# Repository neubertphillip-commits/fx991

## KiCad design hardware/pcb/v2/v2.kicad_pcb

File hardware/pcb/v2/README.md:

# Hauptplatine V2 (Entwurf, nicht bestellfertig)

Tastaturplatine wie V1 plus alles, was sonst lose verdrahtet waere: Der XIAO ESP32S3 liegt mit
der Unterseite zur Platine auf deren Rueckseite und steckt per B2B in einer DF40-Buchse; Kamera,
Mikro und Kamera-Spannungsregler sitzen auf der Platine (Ersatz fuer die Sense-Platine, die mit
~15 mm zu hoch ist). Generator: `hauptplatine_v2.py` (nutzt `../tastatur_pcb.py`).
Vorschau: `vorschau_v2.png` (links vorn, rechts Rueckseite von hinten).

## Was drauf ist

| Ref | Teil | Funktion |
|---|---|---|
| K1-K50 | Kontaktkaemme (ENIG) | Tasten, Matrix 9x7 wie V1 |
| U1, C1, R1, R2 | MCP23017, 100 nF, 2x 4,7 kOhm | Tastatur-Scanner, I2C-Pull-ups |
| J10 | Hirose DF40C-30DS-0.4V (1,5 mm Stapelhoehe) | B2B zum XIAO: 3V3, GND, Kamera, Mikro, SPI, D2 |
| J11 | 8 Bruecken-Pads unter den XIAO-Kantenpads | D0 (INT), D1 (LCD-CS), D3 (Akku-Messung), D4/D5 (I2C), 5V, BAT-Pads |
| J12, U2, U3, FB1, R3, R4, C2-C7 | 24-pol. FPC (0,5 mm), 2x LDO | Kamera OV3660 |
| MIC1, C8 | MSM261D3526H1CPM | PDM-Mikro (GPIO 42 Takt, 41 Daten) |
| J13 | 8 Pads | LT7680-Displayboard: 3V3, GND, SCK, MOSI, MISO, CS (D1), RST (D2), WAIT (frei) |
| J14 | 2 Pads | LiPo (geht ueber J11 an die BAT-Pads des XIAO) |
| J15, D1 | 2 Pads, Schottky 10MQ060N | Qi-Empfaenger -> 5V-Pin des XIAO |
| R5, R6 | 2x 100 kOhm | Akkuspannung halbiert an D3 (statt LT7680-WAIT) |

Montage: XIAO mit Akku-Draehten zuerst auf die DF40-Buchse stecken; die Kantenpads und BAT-Pads
ueberbruecken den 1,5-mm-Spalt mit kurzen Drahtstuecken (Bauteilbeinchen) zu J11.

## Vor der Bestellung (offen, ohne das nicht bestellen)

1. **Lage der B2B-Buchse unter dem XIAO**: aus Seeeds Sense-Platine abgeleitet (Mitte 11,05 / 2,31 mm),
   aber angenommen, dass der Stecker am Ende gegenueber USB sitzt. Am echten XIAO nachmessen
   (Foto der Unterseite mit Lineal genuegt).
2. **DF40-Footprint und Pin-1-Lage**: Reihenabstand (hier 2,2 mm) und Padmasse aus der Hirose-Zeichnung,
   Pin 1 der Buchse gegen Seeeds Sense-Layout pruefen (Belegung siehe `../README.md`).
3. **Kamera-Spannungen**: AVDD 2,8 V ist sicher. DOVDD (FPC-Pin 11) hier 2,8 V, DVDD (Pin 10) ueber U3;
   Seeed nutzt laut Stueckliste ein 1,3-V-LDO, das Netz heisst aber VCC_1V8. Mit Seeeds Schaltplan-PDF
   klaeren (ESP32-S3 braucht >= 2,5 V High-Pegel, also DOVDD nicht 1,8 V). FPC-Pin 24 hat bei Seeed
   eine Diode (D6) - Funktion klaeren.
4. **FPC-Buchse und Pin 1**: Footprint AFC01-S24FCC-00 angenaehert; Pin-Reihenfolge zur Kamera pruefen.
5. **Mikro-Footprint** ist ein Platzhalter (Padlage aus dem Datenblatt uebernehmen; Schalloeffnung oben?).
6. **BAT-Polaritaet** der XIAO-Unterseitenpads (BAT1/BAT2) am XIAO ablesen und J14 beschriften.
7. **Hoehe**: XIAO ueber der Platine ~5 mm (1,5 mm Buchse + ~3,5 mm XIAO); hinter der Platine sind
   ~4 mm gemessen. Rueckdeckel-Wanne messen; sonst Rueckdeckel innen ausfraesen.
8. **Teile bei JLCPCB/LCSC**: DF40C-30DS-0.4V, AFC01-S24FCC-00, MSM261D3526H1CPM, ME6211-LDOs
   auf Verfuegbarkeit pruefen; sonst Ersatzteile mit gleichem Footprint.
9. Firmware: Matrix-Scan fuer V1/V2 (statt der 16 Casio-Leitungen), D3 als Akku-Messung.

## Neu erzeugen

```
python3 hauptplatine_v2.py
java -jar freerouting-2.4.1-executable.jar -de v2.dsn -do v2.ses -mp 60   # Java 25
python3 hauptplatine_v2.py --ses v2.ses
```

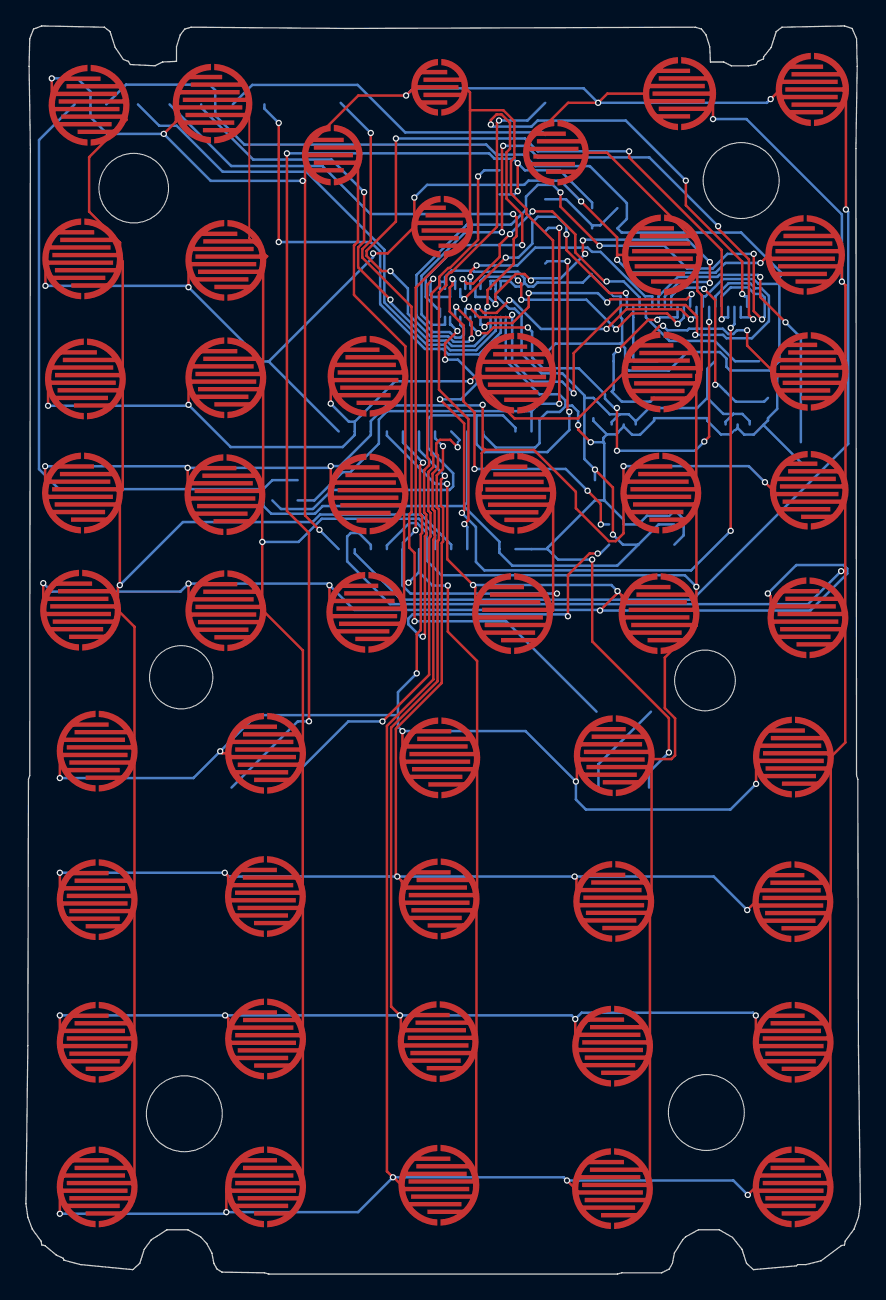
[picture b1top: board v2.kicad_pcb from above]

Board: 2 copper layers, 65.9 x 98.6 mm, 83 parts (0 on the bottom side), 52 nets.

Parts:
C1, C7, C8: 100nF
C2, C3, C4, C5, C6: 1uF
C9: 10uF
D1: 10MQ060NTRPBF
FB1: Ferrit 600R
H1, H2, H3, H4, H5, H6: (no value)
J10: DF40C-30DS-0.4V
J11: XIAO-Bruecken
J12: AFC01-S24FCC-00
J13: LT7680
J14: Akku
J15: Qi
K1, K2, K3, K4, K5, K6, K7, K8, K9, K10, K11, K12, K13, K14, K15, K16, K17, K18, K19, K20, K21, K22, K23, K24, K25, K26, K27, K28, K29, K30, K31, K32, K33, K34, K35, K36, K37, K38, K39, K40, K41, K42, K43, K44, K45, K46, K47, K48, K49, K50: Taste
MIC1: MSM261D3526H1CPM
R1, R2: 4.7k
R3, R4: 10k
R5, R6: 100k
U1: MCP23017-E/SO
U2: LDO 2,8V (ME6211C28)
U3: LDO DVDD (pruefen)

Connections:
2V8: C3.1, FB1.1, J12.11, U2.5
3V3: C1.1, C2.1, C4.1, C8.1, C9.1, J10.12, J10.13, J13.1, MIC1.5, R1.1, R2.1, R3.1, U1.9, U1.18, U2.1, U2.3, U3.1, U3.3
5V: D1.1, J11.14
AVDD: C6.1, FB1.2, J12.4
BAT1: J11.23, J14.1, R5.1
BAT2: J11.24, J14.2
C0: K1.2, K9.2, K13.2, K19.2, K25.2, K31.2, K36.2, K41.2, K46.2, U1.21
C1: K2.2, K10.2, K14.2, K20.2, K26.2, K32.2, K37.2, K42.2, K47.2, U1.22
C2: K6.2, K15.2, K21.2, K27.2, K33.2, K38.2, K43.2, K48.2, U1.23
C3: K5.2, K8.2, K16.2, K22.2, K28.2, U1.24
C4: K7.2, K11.2, K17.2, K23.2, K29.2, K34.2, K39.2, K44.2, K49.2, U1.25
C5: K3.2, K12.2, K18.2, K24.2, K30.2, K35.2, K40.2, K45.2, K50.2, U1.26
C6: K4.2, U1.27
CAM_PWDN: J12.8, R4.1
CAM_RST: C7.1, J12.6, R3.2
CAM_SCL: J10.7, J12.5
CAM_SDA: J10.6, J12.3
DVDD: C5.1, J12.10, U3.5
GND: C1.2, C2.2, C3.2, C4.2, C5.2, C6.2, C7.2, C8.2, C9.2, J10.2, J10.3, J10.14, J10.30, J12.2, J12.15, J12.MP1, J12.MP2, J13.2, J15.2, MIC1.2, MIC1.3, R4.2, R6.2, U1.10, U1.15, U1.16, U1.17, U2.2, U3.2
HREF: J10.9, J12.9
INT: J11.1, U1.20
LCD_CS: J11.2, J13.6
LCD_RST: J10.29, J13.7
MISO: J10.27, J13.5
MOSI: J10.26, J13.4
PCLK: J10.22, J12.17
PDM_CLK: J10.4, MIC1.4
PDM_DATA: J10.5, MIC1.1
QI: D1.2, J15.1
R0: K1.1, K2.1, K3.1, K4.1, K5.1, K6.1, K7.1, U1.28
R1: K8.1, K9.1, K10.1, K11.1, K12.1, U1.1
R2: K13.1, K14.1, K15.1, K16.1, K17.1, K18.1, U1.2
R3: K19.1, K20.1, K21.1, K22.1, K23.1, K24.1, U1.3
R4: K25.1, K26.1, K27.1, K28.1, K29.1, K30.1, U1.4
R5: K31.1, K32.1, K33.1, K34.1, K35.1, U1.5
R6: K36.1, K37.1, K38.1, K39.1, K40.1, U1.6
R7: K41.1, K42.1, K43.1, K44.1, K45.1, U1.7
R8: K46.1, K47.1, K48.1, K49.1, K50.1, U1.8
SCK: J10.28, J13.3
SCL: J11.6, R2.2, U1.12
SDA: J11.5, R1.2, U1.13
VBAT_SENSE: J11.4, R5.2, R6.1
VSYNC: J10.8, J12.7
XCLK: J10.25, J12.13
Y2: J10.20, J12.19
Y3: J10.18, J12.21
Y4: J10.17, J12.22
Y5: J10.19, J12.20
Y6: J10.21, J12.18
Y7: J10.23, J12.16
Y8: J10.24, J12.14
Y9: J10.10, J12.12

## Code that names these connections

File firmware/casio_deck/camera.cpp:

#include "camera.h"

#include <Arduino.h>
#include <esp_camera.h>

#include "config.h"

namespace {

// Pinbelegung XIAO ESP32S3 Sense (wie CAMERA_MODEL_XIAO_ESP32S3 im CameraWebServer-Beispiel)
constexpr int CAM_XCLK = 10;
constexpr int CAM_SIOD = 40;
constexpr int CAM_SIOC = 39;
constexpr int CAM_Y9 = 48;
constexpr int CAM_Y8 = 11;
constexpr int CAM_Y7 = 12;
constexpr int CAM_Y6 = 14;
constexpr int CAM_Y5 = 16;
constexpr int CAM_Y4 = 18;
constexpr int CAM_Y3 = 17;
constexpr int CAM_Y2 = 15;
constexpr int CAM_VSYNC = 38;
constexpr int CAM_HREF = 47;
constexpr int CAM_PCLK = 13;

bool on = false;
camera_fb_t* frame = nullptr;
const char* lastError = "";

}  // namespace

namespace camera {

bool begin() {
  if (on) return true;
  camera_config_t cfg = {};
  cfg.pin_pwdn = -1;
  cfg.pin_reset = -1;
  cfg.pin_xclk = CAM_XCLK;
  cfg.pin_sccb_sda = CAM_SIOD;
  cfg.pin_sccb_scl = CAM_SIOC;
  cfg.pin_d7 = CAM_Y9;
  cfg.pin_d6 = CAM_Y8;
  cfg.pin_d5 = CAM_Y7;
  cfg.pin_d4 = CAM_Y6;
  cfg.pin_d3 = CAM_Y5;
  cfg.pin_d2 = CAM_Y4;
  cfg.pin_d1 = CAM_Y3;
  cfg.pin_d0 = CAM_Y2;
  cfg.pin_vsync = CAM_VSYNC;
  cfg.pin_href = CAM_HREF;
  cfg.pin_pclk = CAM_PCLK;
  cfg.xclk_freq_hz = 20000000;
  cfg.ledc_timer = LEDC_TIMER_0;
  cfg.ledc_channel = LEDC_CHANNEL_0;
  cfg.pixel_format = PIXFORMAT_JPEG;
  cfg.frame_size = CAM_FRAME_SIZE;
  cfg.jpeg_quality = CAM_JPEG_QUALITY;
  cfg.fb_count = 1;
  cfg.fb_location = CAMERA_FB_IN_PSRAM;
  cfg.grab_mode = CAMERA_GRAB_LATEST;  // immer das aktuelle Bild, kein altes aus dem Puffer

  esp_err_t err = esp_camera_init(&cfg);
  if (err != ESP_OK) {
    lastError = "Kamera nicht gefunden";
    Serial.printf("[cam] esp_camera_init: 0x%x\n", err);
    return false;
  }
  if (sensor_t* s = esp_camera_sensor_get()) {
    // Das Modul sitzt auf der Sense-Platine gedreht; bei Bedarf hier anpassen.
    s->set_vflip(s, CAM_VFLIP);
    s->set_hmirror(s, CAM_HMIRROR);
    s->set_whitebal(s, 1);
    s->set_awb_gain(s, 1);
    if (s->id.PID == OV3660_PID) {  // wie im CameraWebServer-Beispiel von Espressif
      s->set_brightness(s, 1);
      s->set_saturation(s, -2);
    }
  }
  on = true;
  Serial.println("[cam] an");
  return true;
}

void end() {
  if (!on) return;
  release();
  esp_camera_deinit();
  on = false;
  Serial.println("[cam] aus");
}

bool isOn() { return on; }

bool capture(const uint8_t*& jpeg, size_t& len) {
  if (!on && !begin()) return false;
  release();
  // Weissabgleich und Belichtung regeln nur, solange Bilder abgeholt werden: vor jedem
  // Foto eine Weile Bilder verwerfen (sonst gruenstichig).
  uint32_t warmupStart = millis();
  while (millis() - warmupStart < CAM_WARMUP_MS) {
    if (camera_fb_t* f = esp_camera_fb_get()) esp_camera_fb_return(f);
  }
  frame = esp_camera_fb_get();
  if (!frame) {
    lastError = "Aufnahme fehlgeschlagen";
    return false;
  }
  jpeg = frame->buf;
  len = frame->len;
  return true;
}

void release() {
  if (frame) {
    esp_camera_fb_return(frame);
    frame = nullptr;
  }
}

const char* error() { return lastError; }

}  // namespace camera
